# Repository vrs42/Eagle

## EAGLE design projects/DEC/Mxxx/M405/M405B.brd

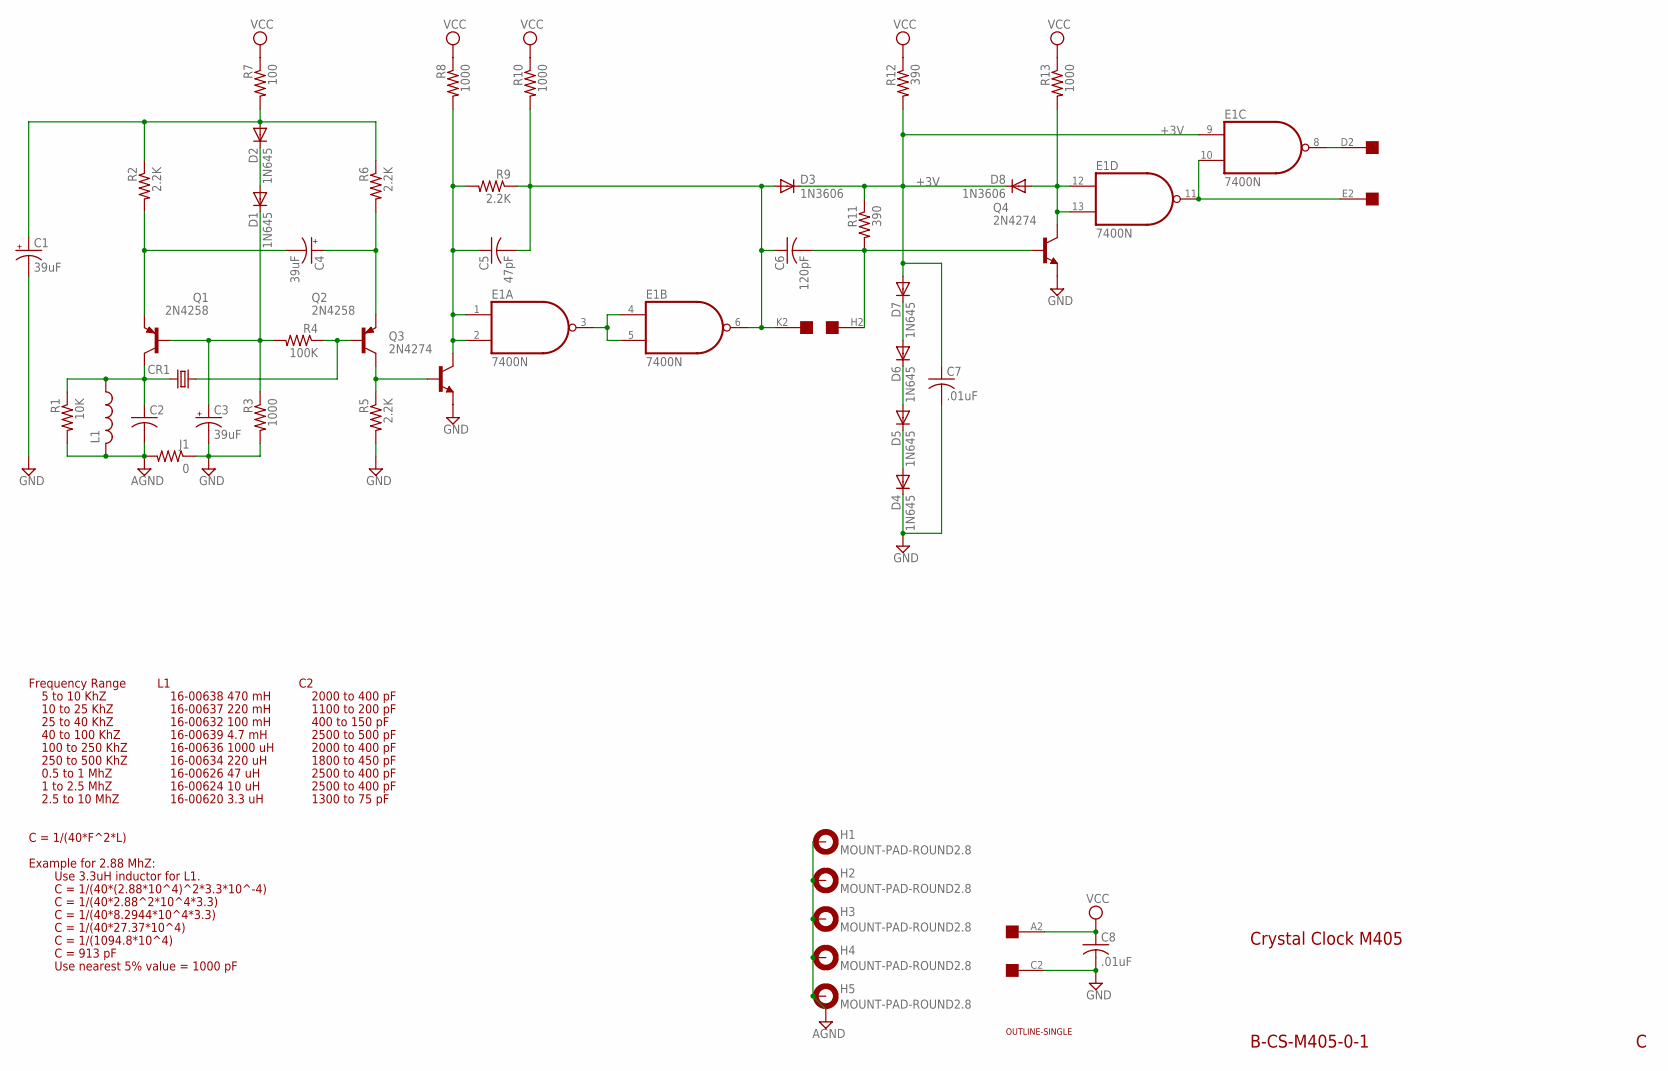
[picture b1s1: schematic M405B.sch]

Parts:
C1, C3, C4: 39uF; E15-5
C2: C-US150-054X183; C150-054X183
C5: 47pF; C050-025X075
C6: 120pF; C050-025X075
C7, C8: .01uF; C050-025X075
CR1: CRYSTALHC13U-H; HC13U-H
D1, D2, D4, D5, D6, D7: 1N645; DO35-10
D3, D8: 1N3606; DO35-10
E1: 7400N; DIL14
H1, H2, H3, H4, H5: MOUNT-PAD-ROUND2.8; 2,8-PAD
J1: 0; 0207/10
L1: L-US0207/12; 0207/12
Q1, Q2: 2N4258; TO39
Q3, Q4: 2N4274; TO39
R1: 10K; 0207/10
R2, R5, R6, R9: 2.2K; 0207/10
R3, R8, R10, R13: 1000; 0207/10
R4: 100K; 0207/10
R7: 100; 0207/10
R11, R12: 390; 0207/10
U$1: OUTLINE-SINGLE; SINGLE
U$2: EDGE-1; EDGE-CON1

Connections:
+3V: C7.1, D3.C, D7.A, D8.C, E1.9 (I0), R11.1, R12.2
AGND: C2.2, H1.B2,8, H2.B2,8, H3.B2,8, H4.B2,8, H5.B2,8, J1.2, L1.2, R1.2
GND: C1.-, C3.-, C7.2, C8.2, D4.C, E1.7 (GND), J1.1, Q3.1 (E), Q4.1 (E), R3.2, R5.2, U$2.C2
unnamed: CR1.1, Q2.2 (B), R4.1
unnamed: C4.-, Q1.1 (E), R2.2
unnamed: C3.+, D1.C, Q1.2 (B), R3.1, R4.2
unnamed: E1.8 (O), U$2.D2
unnamed: C2.1, CR1.2, L1.1, Q1.3 (C), R1.1
unnamed: D1.A, D2.C
unnamed: E1.10 (I1), E1.11 (O), U$2.E2
unnamed: C4.+, Q2.1 (E), R6.2
unnamed: C1.+, D2.A, R2.1, R6.1, R7.2
unnamed: Q2.3 (C), Q3.2 (B), R5.1
unnamed: C5.1, E1.1 (I0), E1.2 (I1), Q3.3 (C), R8.2, R9.2
unnamed: D8.A, E1.12 (I0), E1.13 (I1), Q4.3 (C), R13.2
unnamed: C5.2, C6.1, D3.A, E1.6 (O), R9.1, R10.2, U$2.K2
unnamed: E1.3 (O), E1.4 (I0), E1.5 (I1)
unnamed: D6.A, D7.C
unnamed: C6.2, Q4.2 (B), R11.2, U$2.H2
unnamed: D5.A, D6.C
unnamed: D4.A, D5.C
VCC: C8.1, E1.14 (VCC), R7.1, R8.1, R10.1, R12.1, R13.1, U$2.A2

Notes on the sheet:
Crystal Clock M405
B-CS-M405-0-1
Frequency Range
16-00638 470 mH
16-00637 220 mH
16-00632 100 mH
16-00639 4.7 mH
16-00636 1000 uH
16-00634 220 uH
16-00626 47 uH
16-00624 10 uH
16-00620 3.3 uH
5 to 10 KhZ
10 to 25 KhZ
25 to 40 KhZ
100 to 250 KhZ
250 to 500 KhZ
0.5 to 1 MhZ
1 to 2.5 MhZ
2.5 to 10 MhZ
40 to 100 KhZ
2000 to 400 pF
1100 to 200 pF
400 to 150 pF
2500 to 500 pF
1800 to 450 pF
2500 to 400 pF
1300 to 75 pF
C = 1/(40*F^2*L)
Example for 2.88 MhZ:
C = 1/(40*(2.88*10^4)^2*3.3*10^-4)
Use 3.3uH inductor for L1.
C = 1/(40*2.88^2*10^4*3.3)
C = 1/(40*8.2944*10^4*3.3)
C = 1/(40*27.37*10^4)
C = 1/(1094.8*10^4)
C = 913 pF
Use nearest 5% value = 1000 pF

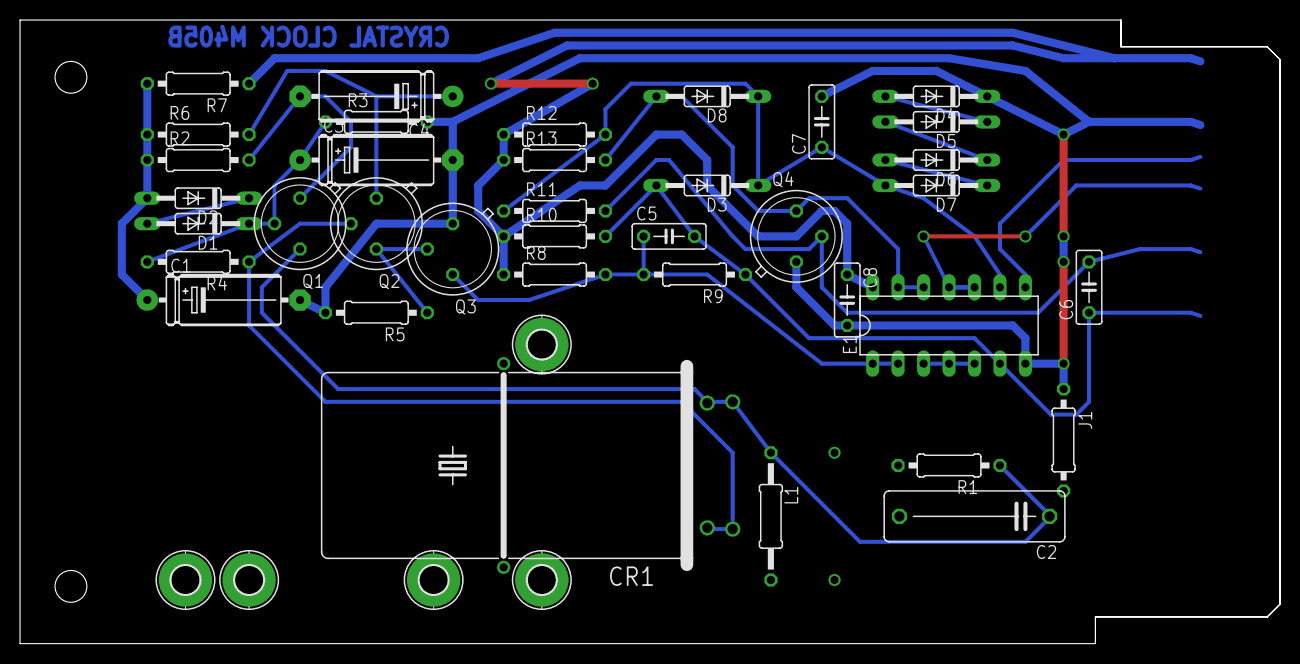
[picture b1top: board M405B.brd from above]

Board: 2 copper layers, 125.7 x 62.2 mm, 44 parts (0 on the bottom side), 22 nets.

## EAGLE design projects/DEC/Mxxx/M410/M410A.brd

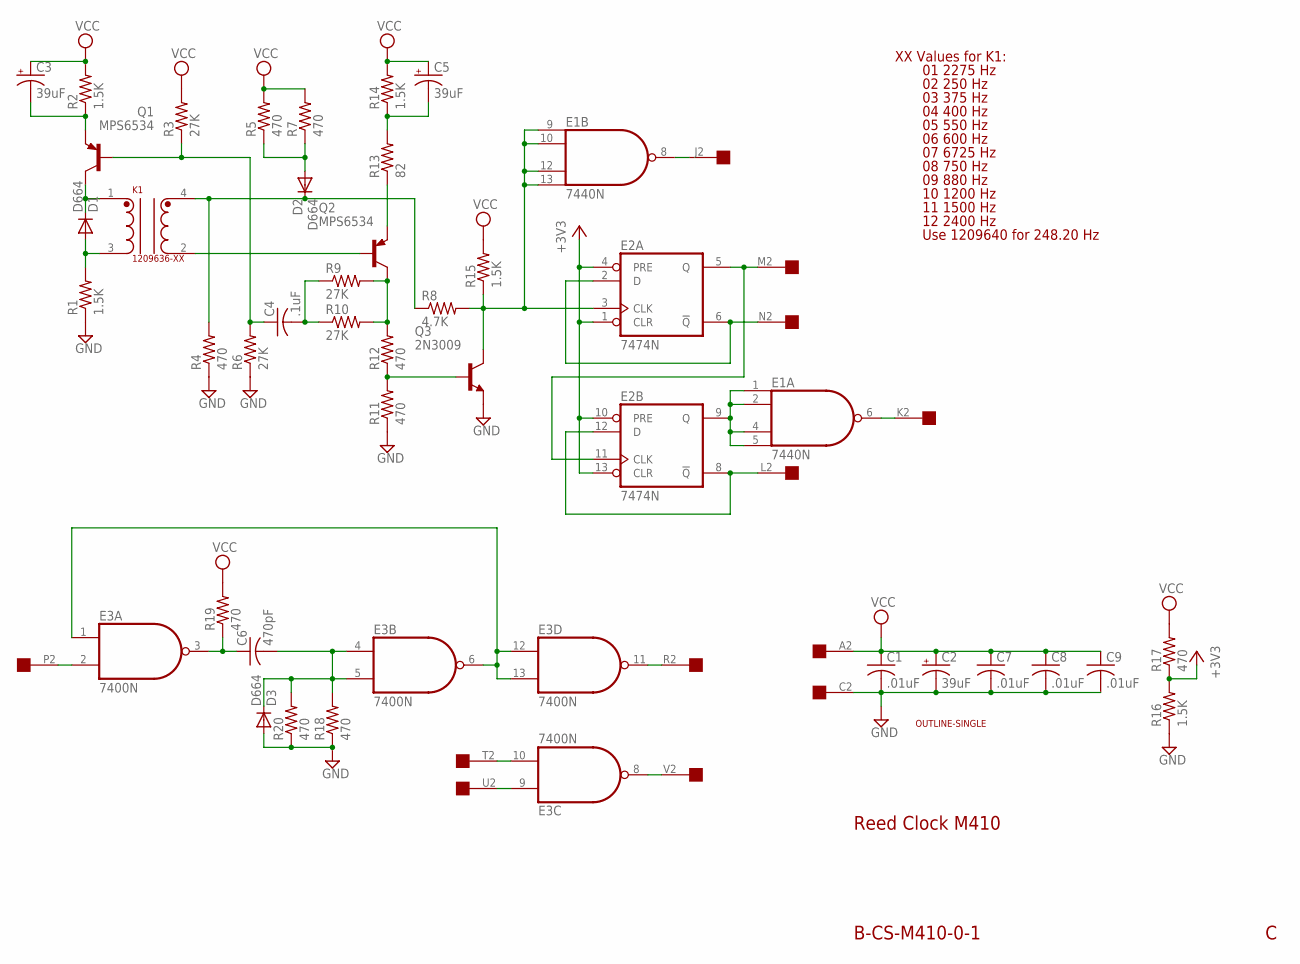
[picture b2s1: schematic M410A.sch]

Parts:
C1, C7, C8, C9: .01uF; C050-025X075
C2, C3, C5: 39uF; E12-8
C4: .1uF; C150-054X183
C6: 470pF; C075-032X103
D1, D2, D3: D664; DO35-10
E1: 7440N; DIL14
E2: 7474N; DIL14
E3: 7400N; DIL14
K1: 1209636-XX; RESONATOR
Q1, Q2: MPS6534; TO5
Q3: 2N3009; TO5
R1, R2, R14, R15, R16: 1.5K; 0207/10
R3, R6, R9, R10: 27K; 0207/10
R4, R5, R7, R11, R12, R17, R18, R19, R20: 470; 0207/10
R8: 4.7K; 0207/10
R13: 82; 0207/10
U$1: OUTLINE-SINGLE; SINGLE
U$3: EDGE-1; EDGE-CON1

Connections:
+3V3: E2.1 (CLR), E2.4 (PRE), E2.10 (PRE), E2.13 (CLR), R16.2, R17.1
GND: C1.2, C2.-, C7.2, C8.2, C9.2, D3.A, E1.7 (GND), E2.7 (GND), E3.7 (GND), Q3.1 (E), R1.1, R4.1, R6.1, R11.1, R16.1, R18.1, R20.1, U$3.C2
unnamed: E3.8 (O), U$3.V2
unnamed: E3.10 (I1), U$3.T2
unnamed: E3.9 (I0), U$3.U2
unnamed: E3.1 (I0), E3.6 (O), E3.12 (I0), E3.13 (I1)
unnamed: E3.11 (O), U$3.R2
unnamed: C6.2, D3.C, E3.4 (I0), E3.5 (I1), R18.2, R20.2
unnamed: C6.1, E3.3 (O), R19.1
unnamed: E2.2 (D), E2.6 (!Q), U$3.N2
unnamed: E2.5 (Q), E2.11 (CLK), U$3.M2
unnamed: E2.8 (!Q), E2.12 (D), U$3.L2
unnamed: E1.1 (I0), E1.2 (I1), E1.4 (I2), E1.5 (I3), E2.9 (Q)
unnamed: E1.6 (O), U$3.K2
unnamed: C3.-, Q1.1 (E), R2.1
unnamed: E1.9 (I0), E1.10 (I1), E1.12 (I2), E1.13 (I3), E2.3 (CLK), Q3.3 (C), R8.2, R15.1
unnamed: E1.8 (O), U$3.J2
unnamed: E3.2 (I1), U$3.P2
unnamed: D1.A, K1.3, R1.2
unnamed: D1.C, K1.1, Q1.3 (C)
unnamed: C4.1, Q1.2 (B), R3.1, R6.2
unnamed: D2.A, R5.1, R7.1
unnamed: K1.2, Q2.2 (B)
unnamed: D2.C, K1.4, R4.2, R8.1
unnamed: C4.2, R9.1, R10.1
unnamed: Q2.3 (C), R9.2, R10.2, R12.2
unnamed: C5.-, R13.2, R14.1
unnamed: Q2.1 (E), R13.1
unnamed: Q3.2 (B), R11.2, R12.1
VCC: C1.1, C2.+, C3.+, C5.+, C7.1, C8.1, C9.1, E1.14 (VCC), E2.14 (VCC), E3.14 (VCC), R2.2, R3.2, R5.2, R7.2, R14.2, R15.2, R17.2, R19.2, U$3.A2

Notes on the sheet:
B-CS-M410-0-1
Reed Clock M410
XX Values for K1:
01 2275 Hz
02 250 Hz
03 375 Hz
04 400 Hz
05 550 Hz
06 600 Hz
07 6725 Hz
08 750 Hz
09 880 Hz
10 1200 Hz
11 1500 Hz
12 2400 Hz
Use 1209640 for 248.20 Hz

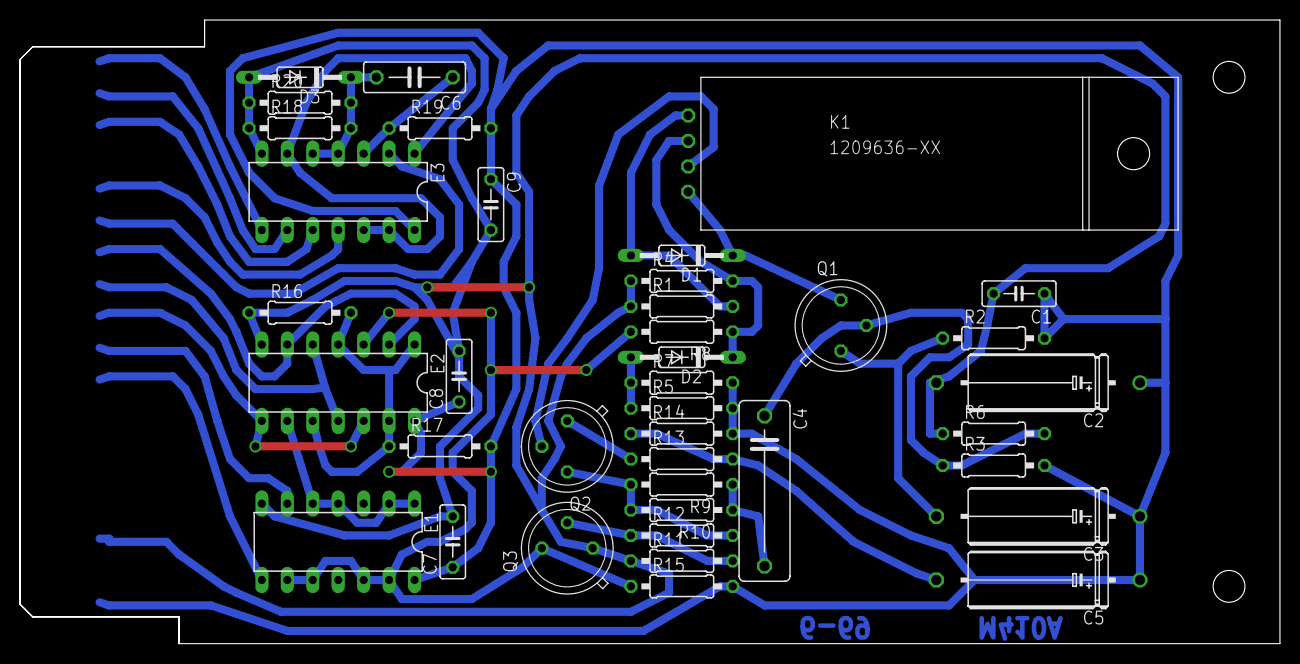
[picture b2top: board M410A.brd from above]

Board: 2 copper layers, 125.7 x 62.2 mm, 41 parts (0 on the bottom side), 30 nets.

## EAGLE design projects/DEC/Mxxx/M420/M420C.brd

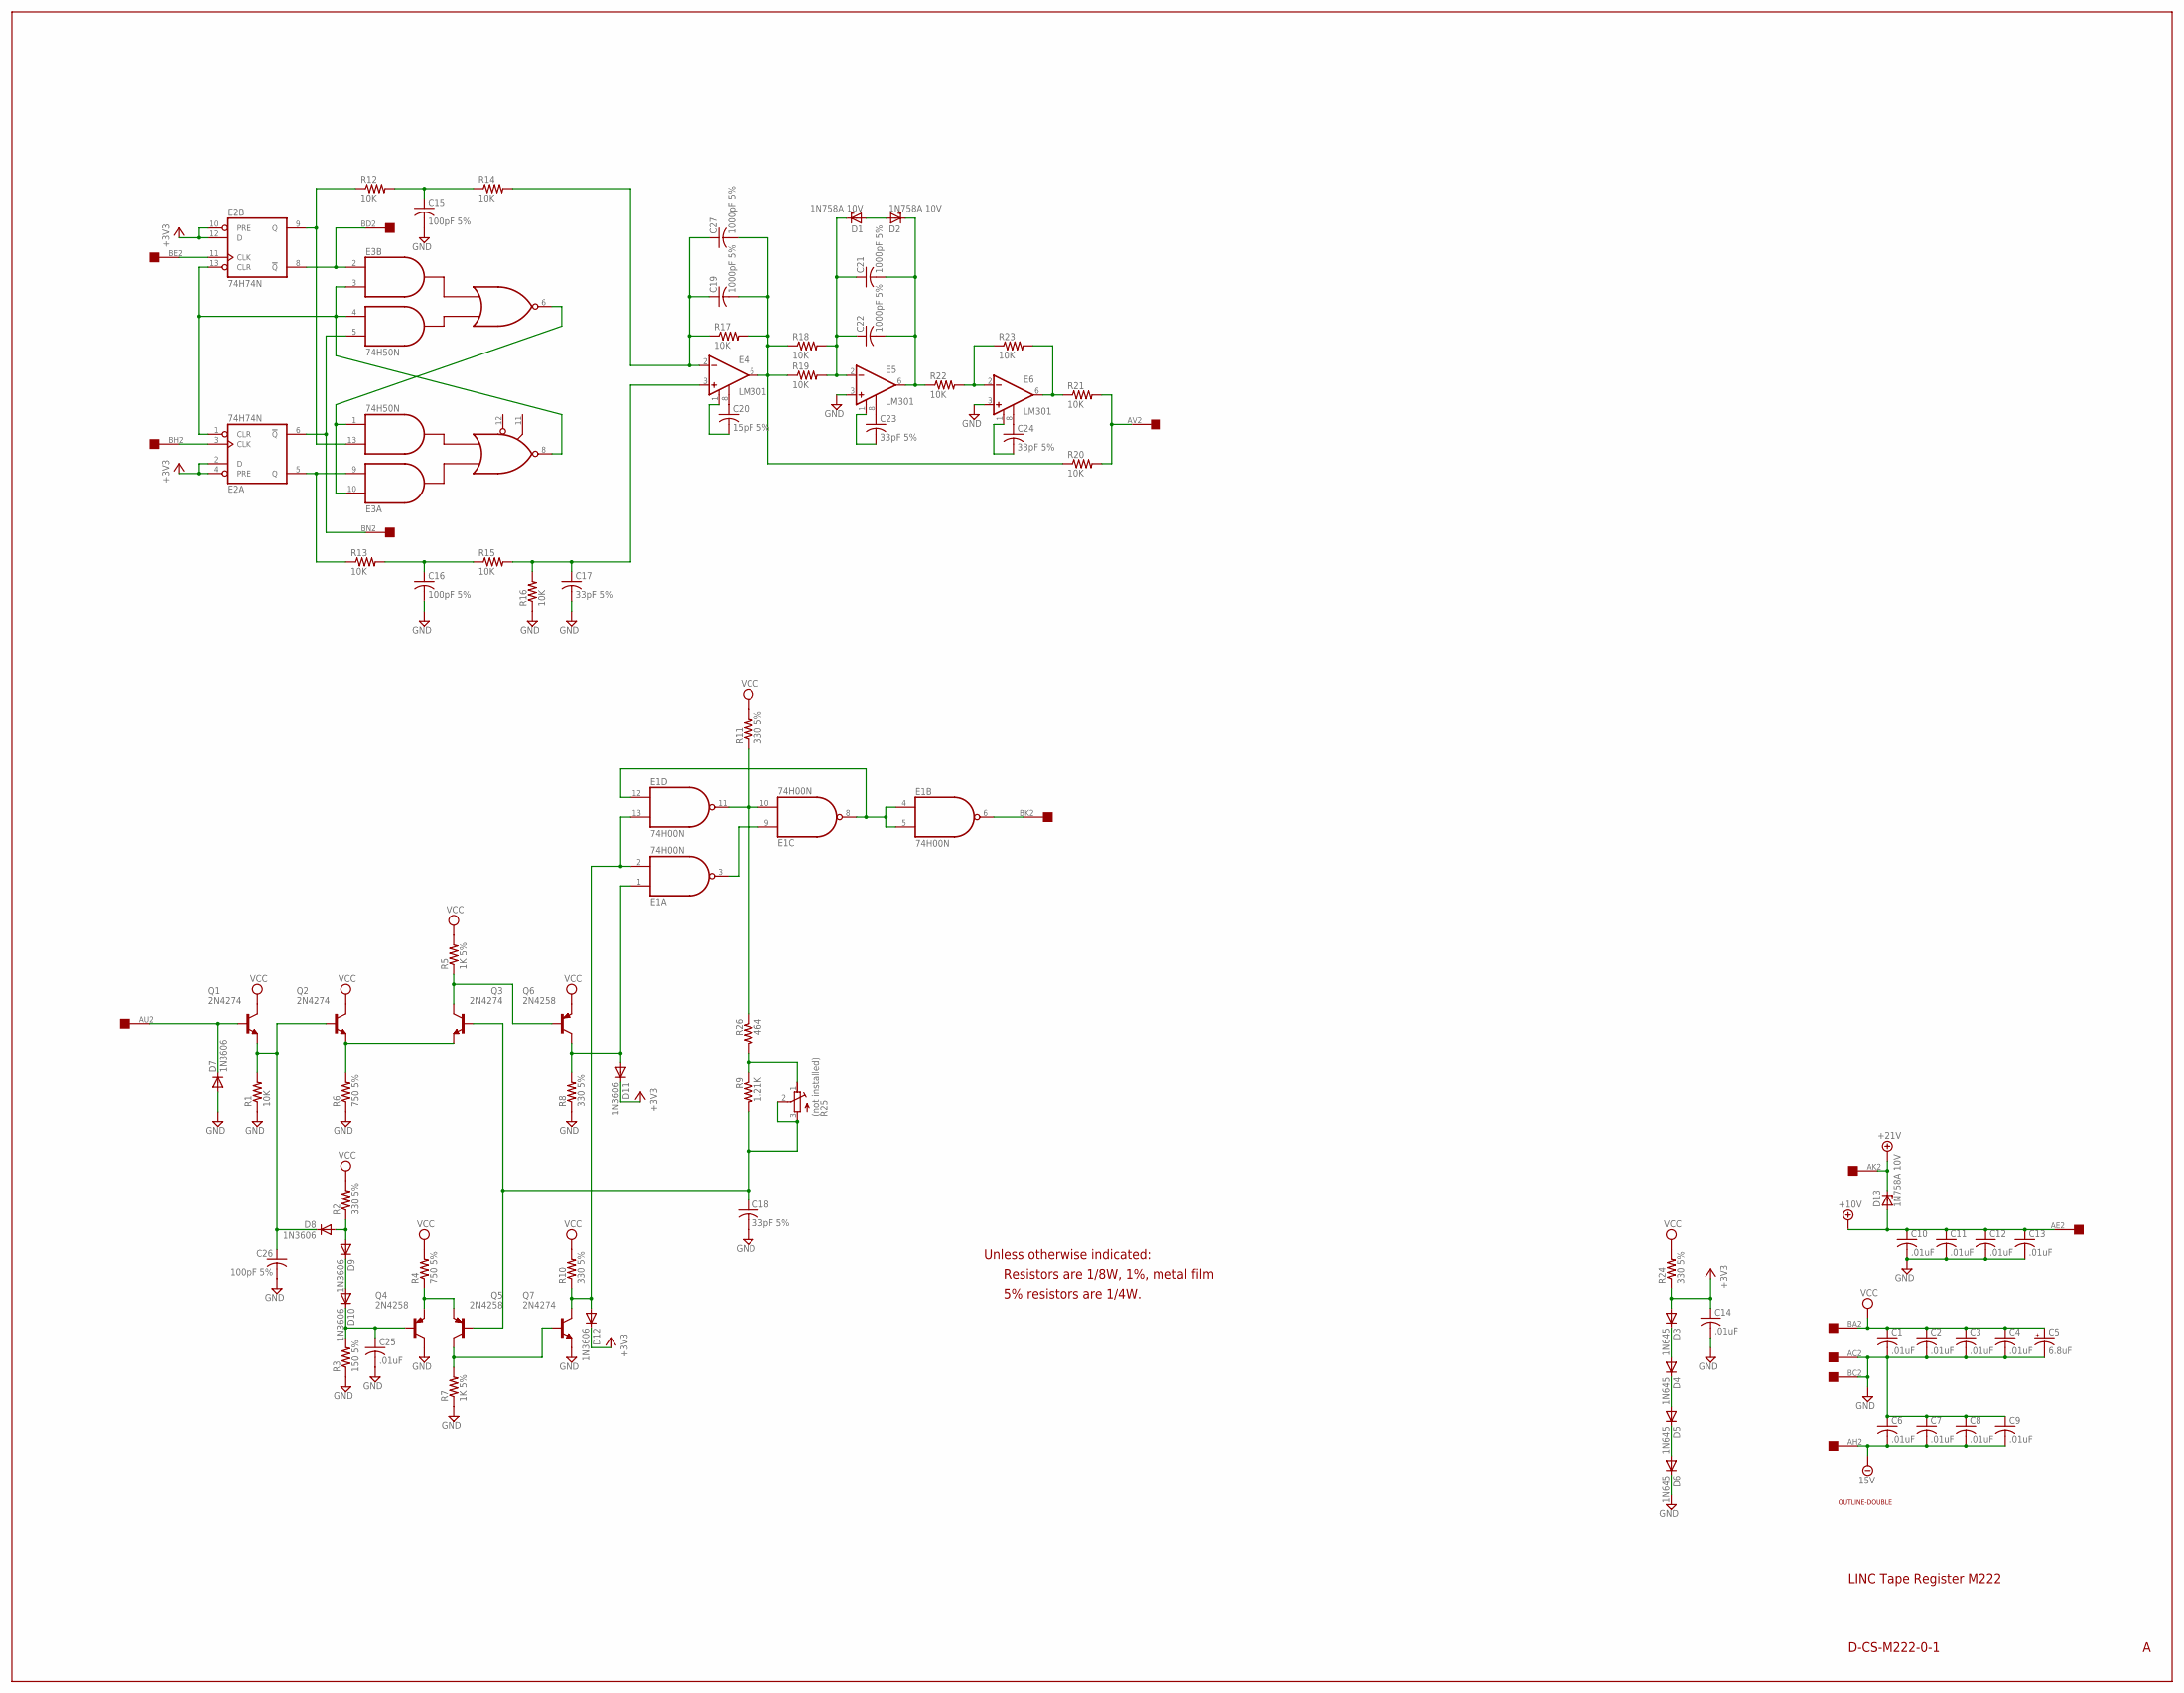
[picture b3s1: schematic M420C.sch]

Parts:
C1, C2, C3, C4, C6, C7, C8, C9, C10, C11, C12, C13, C14, C25: .01uF; C050-025X075
C5: 6.8uF; E12-8
C15, C16, C26: 100pF 5%; C050-025X075
C17, C18, C23, C24: 33pF 5%; C050-025X075
C19, C21, C22, C27: 1000pF 5%; C050-025X075
C20: 15pF 5%; C050-025X075
D1, D2, D13: 1N758A 10V; DO35Z10
D3, D4, D5, D6: 1N645; DO35-10
D7, D8, D9, D10, D11, D12: 1N3606; DO35-10
E1: 74H00N; DIL14
E2: 74H74N; DIL14
E3: 74H50N; DIL14
E4, E5, E6: LM301; TO99
Q1, Q2, Q3, Q7: 2N4274; TO5
Q4, Q5, Q6: 2N4258; TO39
R1, R12, R13, R14, R15, R16, R17, R18, R19, R20, R21, R22, R23: 10K; 0207/15
R2, R8, R10, R11, R24: 330 5%; 0207/10
R3: 150 5%; 0207/10
R4, R6: 750 5%; 0207/10
R5, R7: 1K 5%; 0207/10
R9: 1.21K; 0207/15
R25: (not installed); 3006Y
R26: 464; 0207/15
U$1: DOUBLE; EDGE-CON4
U$2: OUTLINE-DOUBLE; DOUBLE

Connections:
+3V3: C14.1, D3.A, D11.C, D12.C, E2.2 (D), E2.4 (PRE), E2.10 (PRE), E2.12 (D), R24.1
+10V: C10.1, C11.1, C12.1, C13.1, D13.A, E4.7 (+10V), E5.7 (+10V), E6.7 (+10V), U$1.AE2
+21V: D13.C, U$1.AK2
-15V: C6.2, C7.2, C8.2, C9.2, E4.4 (-15V), E5.4 (-15V), E6.4 (-15V), U$1.AH2
GND: C1.2, C2.2, C3.2, C4.2, C5.-, C6.1, C7.1, C8.1, C9.1, C10.2, C11.2, C12.2, C13.2, C14.2, C15.2, C16.2, C17.2, C18.2, C25.2, C26.2, D6.C, D7.A, E1.7 (GND), E2.7 (GND), E3.7 (GND), E5.3 (+IN), E6.3 (+IN), Q4.3 (C), Q7.1 (E), R1.1, R3.1, R6.1, R7.1, R8.1, R16.1, U$1.AC2, U$1.BC2
unnamed: E2.1 (CLR), E2.13 (CLR), E3.3 (I2), E3.4 (I3), E3.8 (O)
unnamed: E3.1 (I4), E3.6 (O), E3.10 (I1)
unnamed: E2.8 (!Q), E3.2 (I1), U$1.BD2
unnamed: E2.6 (!Q), E3.5 (I4), U$1.BN2
unnamed: E2.3 (CLK), U$1.BH2
unnamed: C17.1, E4.3 (+IN), R15.2, R16.2
unnamed: C15.1, R12.2, R14.1
unnamed: E2.9 (Q), E3.13 (I3), R12.1
unnamed: E2.5 (Q), E3.9 (I2), R13.1
unnamed: E2.11 (CLK), U$1.BE2
unnamed: D3.C, D4.A
unnamed: C16.1, R13.2, R15.1
unnamed: C20.1, E4.8 (CMP)
unnamed: D5.C, D6.A
unnamed: C19.1, C27.1, E4.2 (-IN), R14.2, R17.1
unnamed: C20.2, E4.1 (ON/CMP)
unnamed: C19.2, C27.2, E4.6 (OUT), R17.2, R18.1, R19.1, R20.1
unnamed: C21.1, C22.1, D1.C, E5.2 (-IN), R18.2, R19.2
unnamed: D4.C, D5.A
unnamed: C21.2, C22.2, D2.C, E5.6 (OUT), R22.1
unnamed: D1.A, D2.A
unnamed: C23.1, E5.8 (CMP)
unnamed: C23.2, E5.1 (ON/CMP)
unnamed: E6.2 (-IN), R22.2, R23.1
unnamed: C24.1, E6.8 (CMP)
unnamed: C24.2, E6.1 (ON/CMP)
unnamed: E6.6 (OUT), R21.1, R23.2
unnamed: R20.2, R21.2, U$1.AV2
unnamed: E1.6 (O), U$1.BK2
unnamed: E1.4 (I0), E1.5 (I1), E1.8 (O), E1.12 (I0)
unnamed: E1.10 (I1), E1.11 (O), R11.1, R26.1
unnamed: D12.A, E1.2 (I1), E1.13 (I1), Q7.3 (C), R10.1
unnamed: D11.A, E1.1 (I0), Q6.3 (C), R8.2
unnamed: E1.3 (O), E1.9 (I0)
unnamed: D7.C, Q1.2 (B), U$1.AU2
unnamed: C26.1, D8.C, Q1.1 (E), Q2.2 (B), R1.2
unnamed: Q2.1 (E), Q3.1 (E), R6.2
unnamed: Q3.3 (C), Q6.2 (B), R5.1
unnamed: C18.1, Q3.2 (B), Q5.2 (B), R9.2, R25.2 (S), R25.3 (E)
unnamed: Q4.1 (E), Q5.1 (E), R4.1
unnamed: Q5.3 (C), Q7.2 (B), R7.2
unnamed: R9.1, R25.1 (A), R26.2
unnamed: D8.A, D9.A, R2.1
unnamed: D9.C, D10.A
unnamed: C25.1, D10.C, Q4.2 (B), R3.2
VCC: C1.1, C2.1, C3.1, C4.1, C5.+, E1.14 (VCC), E2.14 (VCC), E3.14 (VCC), Q1.3 (C), Q2.3 (C), Q6.1 (E), R2.2, R4.2, R5.2, R10.2, R11.2, R24.2, U$1.BA2

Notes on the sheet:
LINC Tape Register M222
D-CS-M222-0-1
Unless otherwise indicated:
Resistors are 1/8W, 1%, metal film
5% resistors are 1/4W.

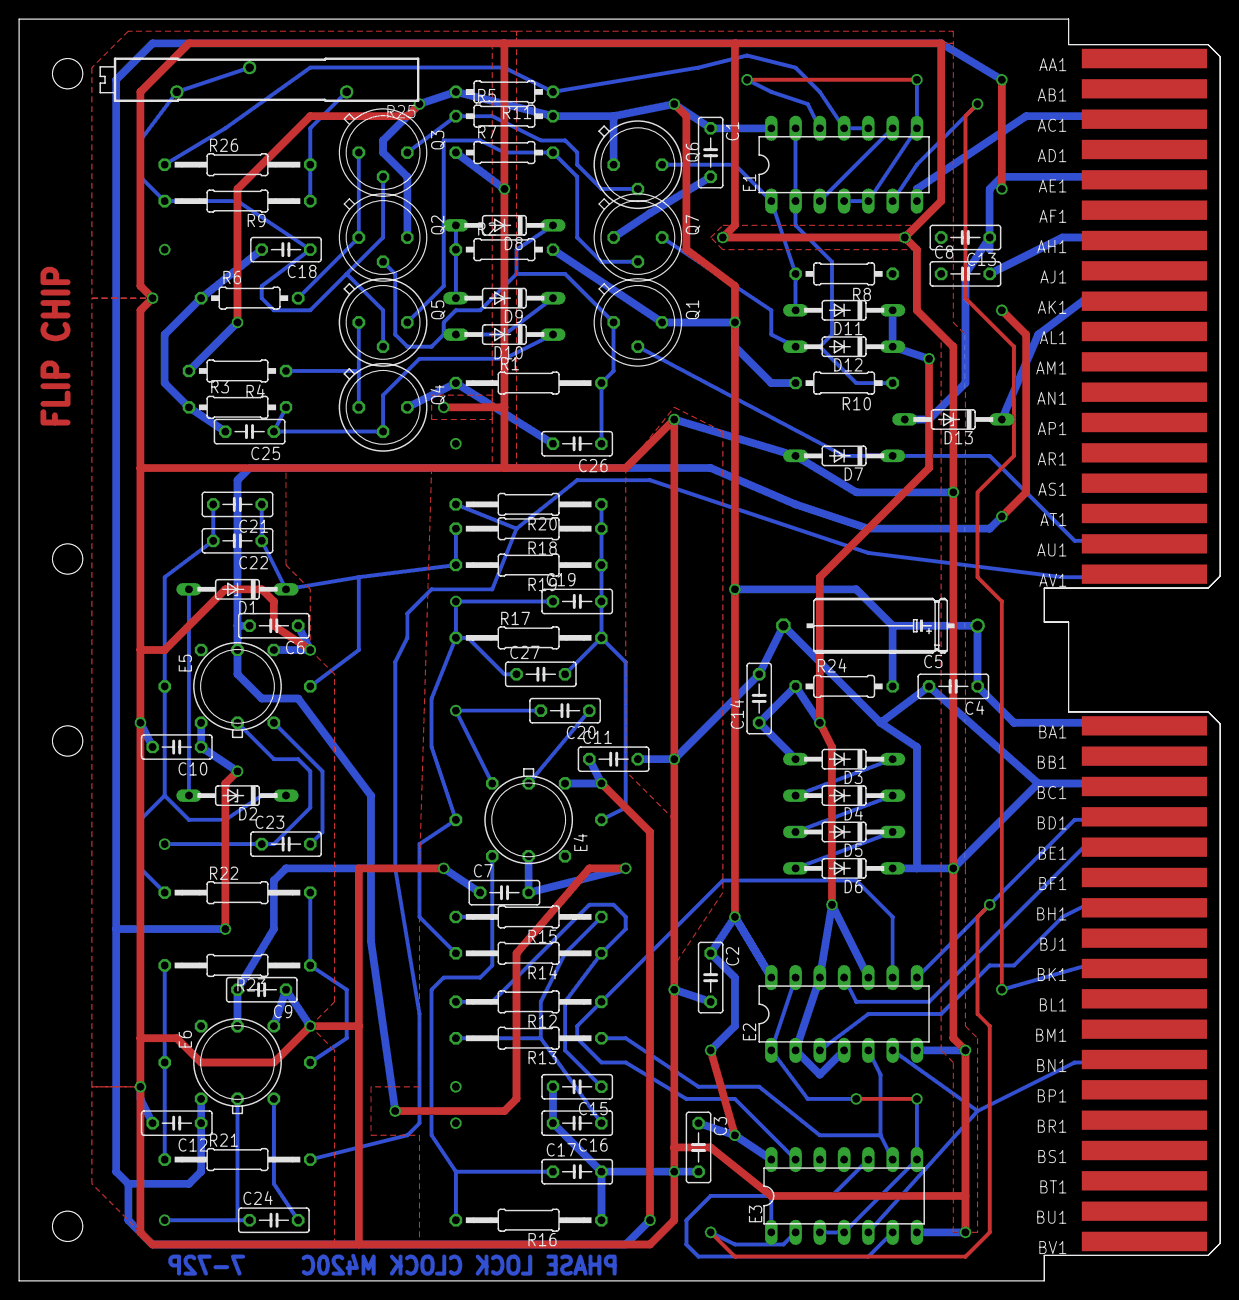
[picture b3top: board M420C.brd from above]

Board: 2 copper layers, 125.7 x 132.1 mm, 82 parts (0 on the bottom side), 51 nets.

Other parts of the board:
U$4: FLIPCHIP

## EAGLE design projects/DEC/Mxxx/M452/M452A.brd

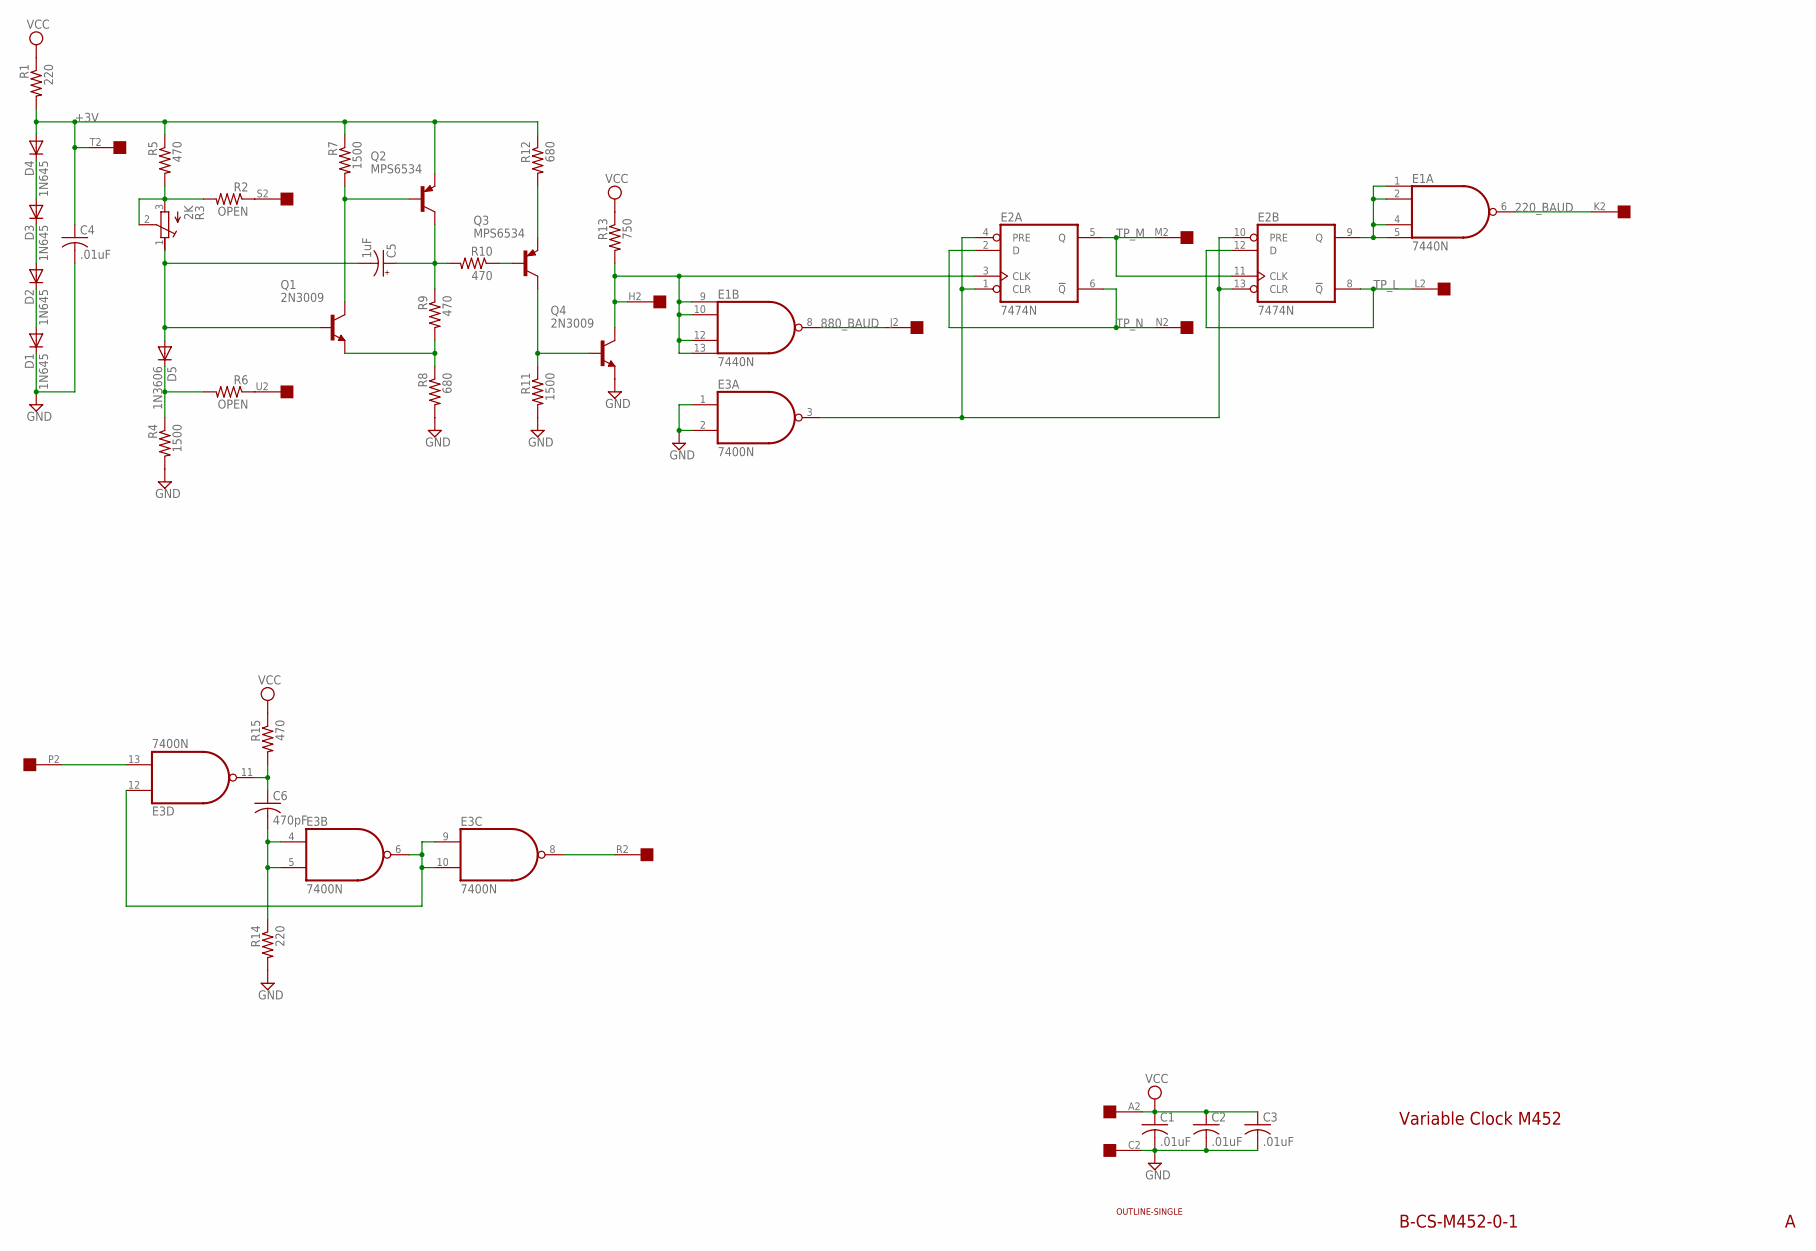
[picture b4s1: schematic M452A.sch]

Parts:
C1, C2, C3, C4: .01uF; C050-025X075
C5: 1uF; E15-5
C6: 470pF; C150-054X183
D1, D2, D3, D4: 1N645; DO35-10
D5: 1N3606; DO35-10
E1: 7440N; DIL14
E2: 7474N; DIL14
E3: 7400N; DIL14
Q1, Q4: 2N3009; TO39
Q2, Q3: MPS6534; TO39
R1, R14: 220; 0207/10
R2, R6: OPEN; 0207/10
R3: 2K; 3006Y
R4, R7, R11: 1500; 0207/10
R5, R9, R10, R15: 470; 0207/10
R8, R12: 680; 0207/10
R13: 750; 0207/10
U$1: OUTLINE-SINGLE; SINGLE
U$2: EDGE-1; EDGE-CON1

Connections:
220_BAUD: E1.6 (O), U$2.K2
880_BAUD: E1.8 (O), U$2.J2
+3V: C4.1, D4.A, Q2.1 (E), R1.2, R5.1, R7.1, R12.1, U$2.T2
GND: C1.2, C2.2, C3.2, C4.2, D1.C, E1.7 (GND), E2.7 (GND), E3.1 (I0), E3.2 (I1), E3.7 (GND), Q4.1 (E), R4.2, R8.2, R11.2, R14.2, U$2.C2
unnamed: C5.+, Q2.3 (C), R9.1, R10.2
unnamed: C5.-, D5.A, Q1.2 (B), R3.1 (A)
unnamed: Q1.1 (E), R8.1, R9.2
unnamed: E1.1 (I0), E1.2 (I1), E1.4 (I2), E1.5 (I3), E2.9 (Q)
unnamed: Q1.3 (C), Q2.2 (B), R7.2
unnamed: R2.2, R3.2 (S), R3.3 (E), R5.2
unnamed: D5.C, R4.1, R6.2
unnamed: Q3.2 (B), R10.1
unnamed: Q3.1 (E), R12.2
unnamed: Q3.3 (C), Q4.2 (B), R11.1
unnamed: E2.1 (CLR), E2.4 (PRE), E2.10 (PRE), E2.13 (CLR), E3.3 (O)
unnamed: E3.13 (I1), U$2.P2
unnamed: E1.9 (I0), E1.10 (I1), E1.12 (I2), E1.13 (I3), E2.3 (CLK), Q4.3 (C), R13.2, U$2.H2
unnamed: C6.2, E3.4 (I0), E3.5 (I1), R14.1
unnamed: D3.A, D4.C
unnamed: C6.1, E3.11 (O), R15.2
unnamed: E3.6 (O), E3.9 (I0), E3.10 (I1), E3.12 (I0)
unnamed: D2.A, D3.C
unnamed: D1.A, D2.C
unnamed: E3.8 (O), U$2.R2
unnamed: R6.1, U$2.U2
unnamed: R2.1, U$2.S2
TP_L: E2.8 (!Q), E2.12 (D), U$2.L2
TP_M: E2.5 (Q), E2.11 (CLK), U$2.M2
TP_N: E2.2 (D), E2.6 (!Q), U$2.N2
VCC: C1.1, C2.1, C3.1, E1.14 (VCC), E2.14 (VCC), E3.14 (VCC), R1.1, R13.1, R15.1, U$2.A2

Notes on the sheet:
Variable Clock M452
B-CS-M452-0-1

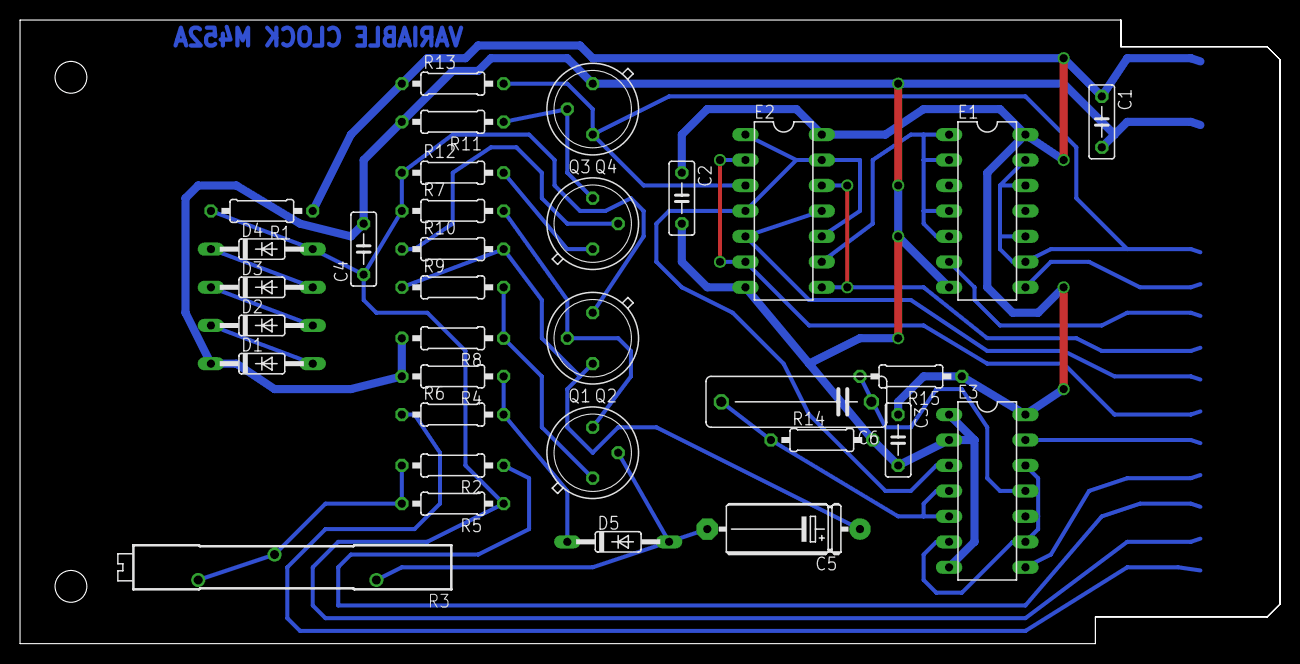
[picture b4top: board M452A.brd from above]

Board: 2 copper layers, 125.7 x 62.2 mm, 35 parts (0 on the bottom side), 30 nets.

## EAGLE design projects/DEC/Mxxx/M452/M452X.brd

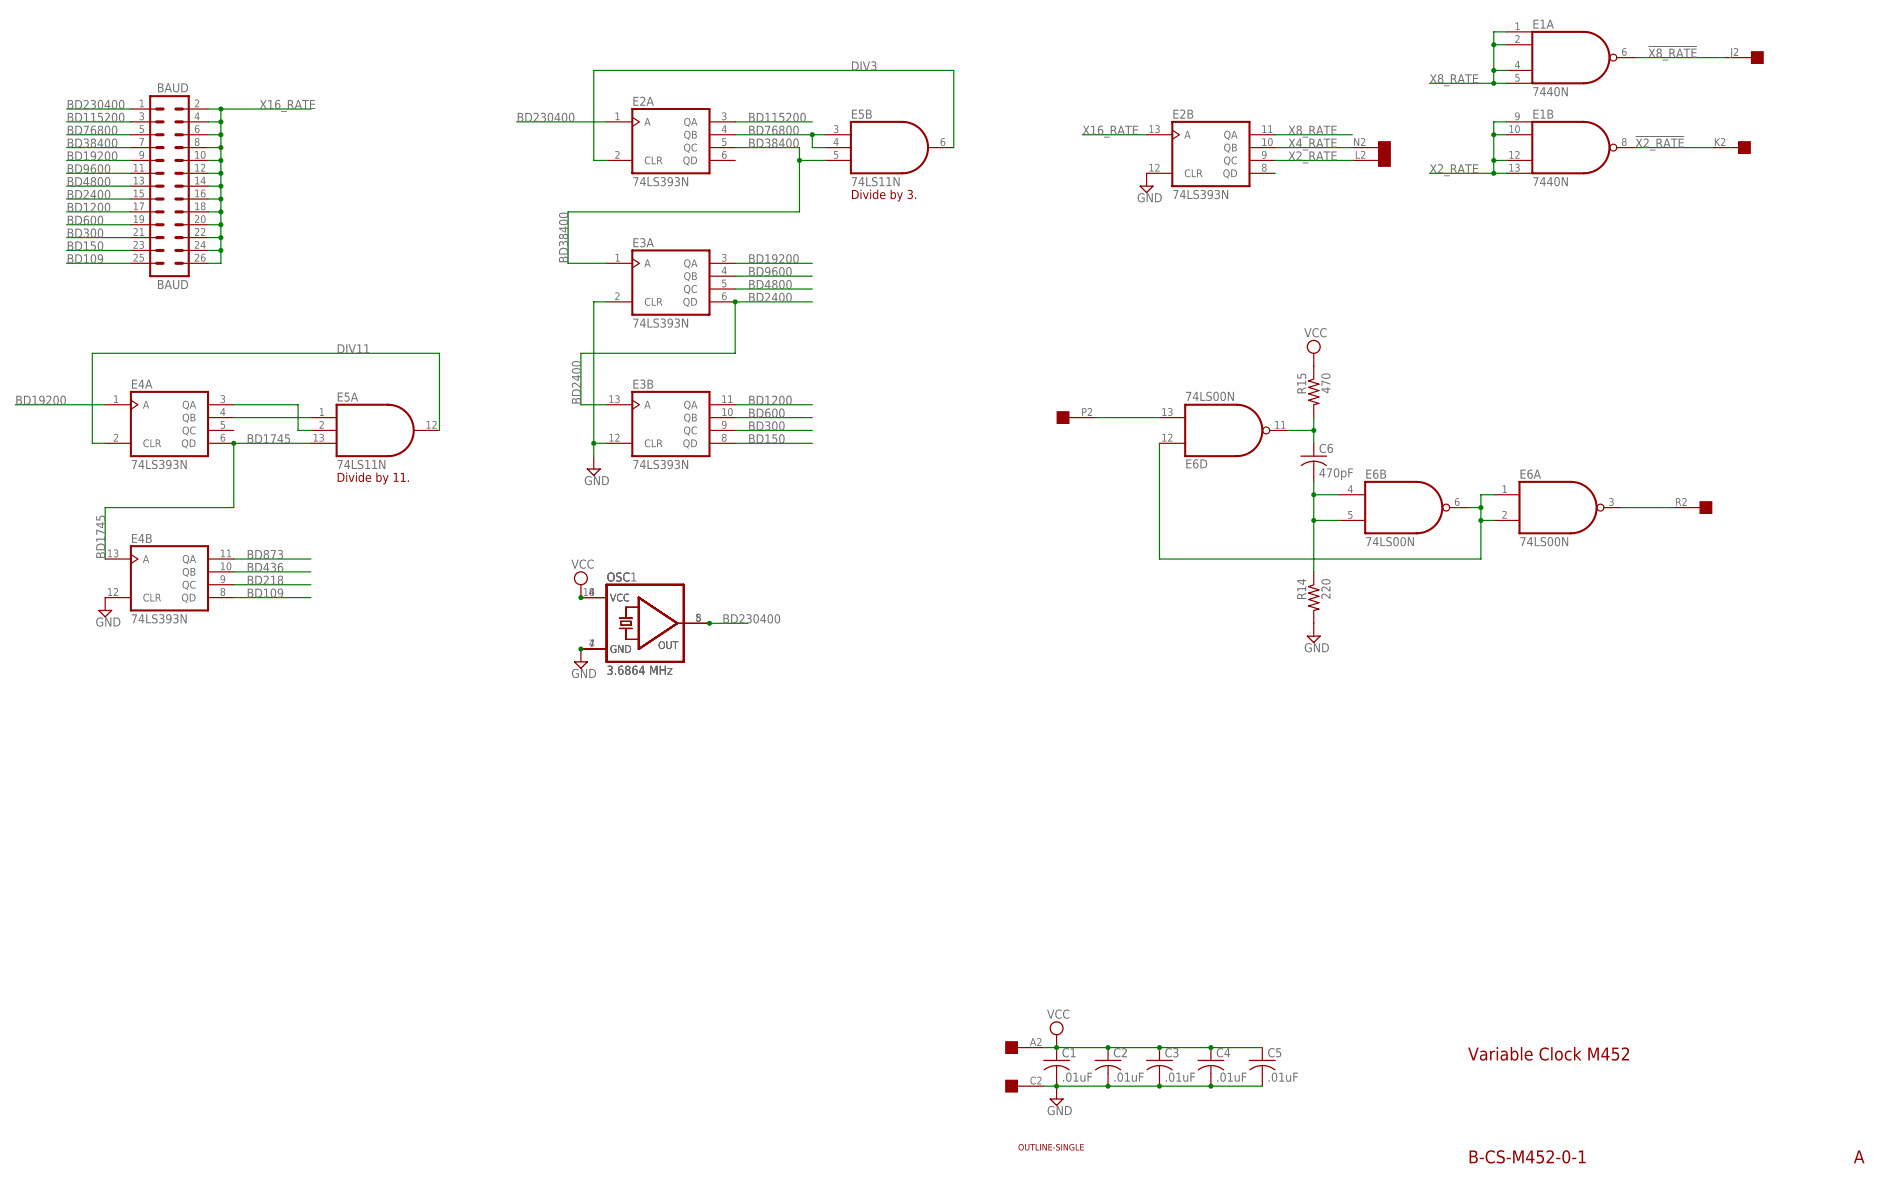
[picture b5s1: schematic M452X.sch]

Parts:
BAUD: BAUD; MA13-2
C1, C2, C3, C4, C5: .01uF; C050-025X075
C6: 470pF; C075-032X103
E1: 7440N; DIL14
E2, E3, E4: 74LS393N; DIL14
E5: 74LS11N; DIL14
E6: 74LS00N; DIL14
OSC: 3.6864 MHz; DIL08S
OSC1: 3.6864 MHz; DIL14S
R14: 220; 0207/10
R15: 470; 0207/10
U$1: OUTLINE-SINGLE; SINGLE
U$2: EDGE-1; EDGE-CON1

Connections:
!X2_RATE: E1.8 (O), U$2.K2
!X8_RATE: E1.6 (O), U$2.J2
BD109: BAUD.25, E4.8 (QD)
BD150: BAUD.23, E3.8 (QD)
BD218: E4.9 (QC)
BD300: BAUD.21, E3.9 (QC)
BD436: E4.10 (QB)
BD600: BAUD.19, E3.10 (QB)
BD873: E4.11 (QA)
BD1200: BAUD.17, E3.11 (QA)
BD1745: E4.6 (QD), E4.13 (A), E5.13 (I2)
BD2400: BAUD.15, E3.6 (QD), E3.13 (A)
BD4800: BAUD.13, E3.5 (QC)
BD9600: BAUD.11, E3.4 (QB)
BD19200: BAUD.9, E3.3 (QA), E4.1 (A)
BD38400: BAUD.7, E2.5 (QC), E3.1 (A), E5.5 (I2)
BD76800: BAUD.5, E2.4 (QB), E5.3 (I0), E5.4 (I1)
BD115200: BAUD.3, E2.3 (QA)
BD230400: BAUD.1, E2.1 (A), OSC.5 (OUT), OSC1.8 (OUT)
DIV3: E2.2 (CLR), E5.6 (O)
DIV11: E4.2 (CLR), E5.12 (O)
GND: C1.2, C2.2, C3.2, C4.2, C5.2, E1.7 (GND), E2.7 (GND), E2.12 (CLR), E3.2 (CLR), E3.7 (GND), E3.12 (CLR), E4.7 (GND), E4.12 (CLR), E5.7 (GND), E6.7 (GND), OSC.4 (GND), OSC1.7 (GND), R14.2, U$2.C2
unnamed: E6.13 (I1), U$2.P2
unnamed: C6.2, E6.4 (I0), E6.5 (I1), R14.1
unnamed: C6.1, E6.11 (O), R15.2
unnamed: E6.1 (I0), E6.2 (I1), E6.6 (O), E6.12 (I0)
unnamed: E6.3 (O), U$2.R2
unnamed: E4.3 (QA), E5.2 (I1)
unnamed: E4.4 (QB), E5.1 (I0)
VCC: C1.1, C2.1, C3.1, C4.1, C5.1, E1.14 (VCC), E2.14 (VCC), E3.14 (VCC), E4.14 (VCC), E5.14 (VCC), E6.14 (VCC), OSC.8 (VCC), OSC1.14 (VCC), R15.1, U$2.A2
X2_RATE: E1.9 (I0), E1.10 (I1), E1.12 (I2), E1.13 (I3), E2.9 (QC), U$2.L2
X4_RATE: E2.10 (QB), U$2.N2
X8_RATE: E1.1 (I0), E1.2 (I1), E1.4 (I2), E1.5 (I3), E2.11 (QA)
X16_RATE: BAUD.2, BAUD.4, BAUD.6, BAUD.8, BAUD.10, BAUD.12, BAUD.14, BAUD.16, BAUD.18, BAUD.20, BAUD.22, BAUD.24, BAUD.26, E2.13 (A)

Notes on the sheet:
Variable Clock M452
B-CS-M452-0-1
Divide by 11.
Divide by 3.
